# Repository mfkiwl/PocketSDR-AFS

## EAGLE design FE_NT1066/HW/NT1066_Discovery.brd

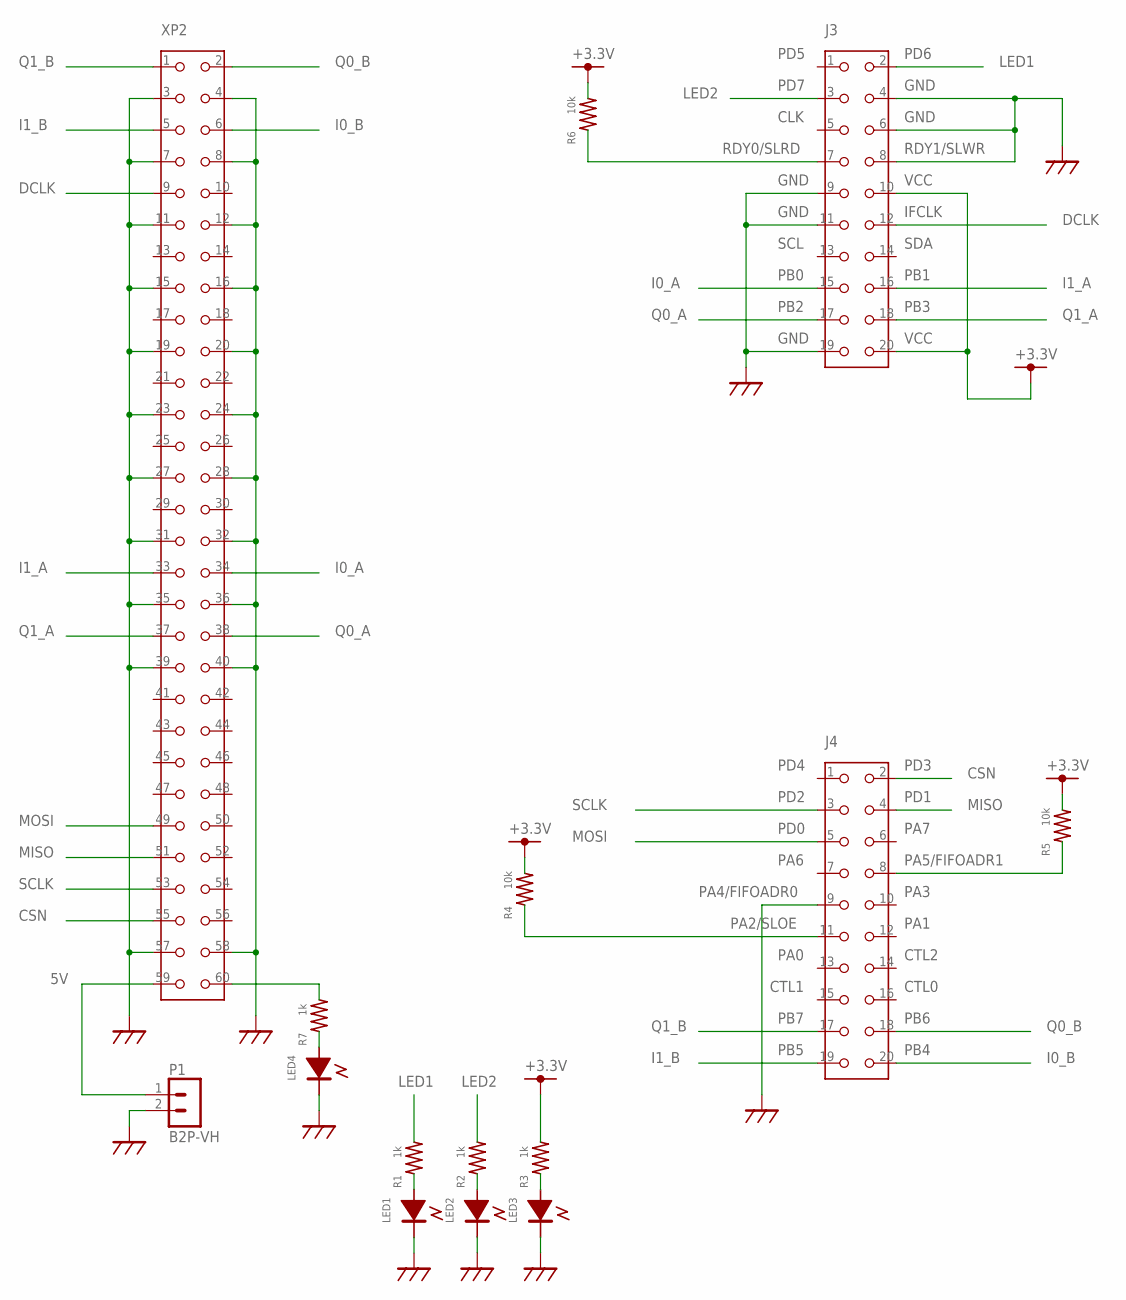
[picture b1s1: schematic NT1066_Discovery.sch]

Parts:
J3, J4: PINH-2.54MM-20P
LED1, LED2, LED3, LED4: LED1608; LED_1608
P1: B2P-VH
R1, R2, R3, R7: 1k; C1608
R4, R5, R6: 10k; C1608
XP2: PINH-2.54MM-60P

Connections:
5V: P1.1, XP2.59
+3.3V: J3.10, J3.20, R3.2, R4.2, R5.2, R6.2
CSN: J4.2, XP2.55
DCLK: J3.12, XP2.9
FIFOADR1: J4.8, R5.1
GND: J3.4, J3.6, J3.8, J3.9, J3.11, J3.19, J4.9, LED1.2, LED2.2, LED3.2, LED4.2, P1.2, XP2.3, XP2.4, XP2.7, XP2.8, XP2.11, XP2.12, XP2.15, XP2.16, XP2.19, XP2.20, XP2.23, XP2.24, XP2.27, XP2.28, XP2.31, XP2.32, XP2.35, XP2.36, XP2.39, XP2.40, XP2.57, XP2.58
I0_A: J3.15, XP2.34
I0_B: J4.20, XP2.6
I1_A: J3.16, XP2.33
I1_B: J4.19, XP2.5
LED1: J3.2, R1.2
LED2: J3.3, R2.2
MISO: J4.4, XP2.51
MOSI: J4.5, XP2.49
unnamed: R7.2, XP2.60
unnamed: LED4.1 (+), R7.1
unnamed: LED3.1 (+), R3.1
unnamed: LED2.1 (+), R2.1
unnamed: LED1.1 (+), R1.1
Q0_A: J3.17, XP2.38
Q0_B: J4.18, XP2.2
Q1_A: J3.18, XP2.37
Q1_B: J4.17, XP2.1
SCLK: J4.3, XP2.53
SLOE: J4.11, R4.1
SLRD: J3.7, R6.1

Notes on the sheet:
RDY1/SLWR
PD6
GND
VCC
IFCLK
SDA
PB1
PB3
PD5
PD7
CLK
RDY0/SLRD
SCL
PB0
PB2
PD4
PD2
PD0
PA6
PA4/FIFOADR0
PA2/SLOE
PA0
CTL1
PB7
PB5
PB4
PB6
CTL0
CTL2
PA1
PA3
PA5/FIFOADR1
PA7
PD1
PD3

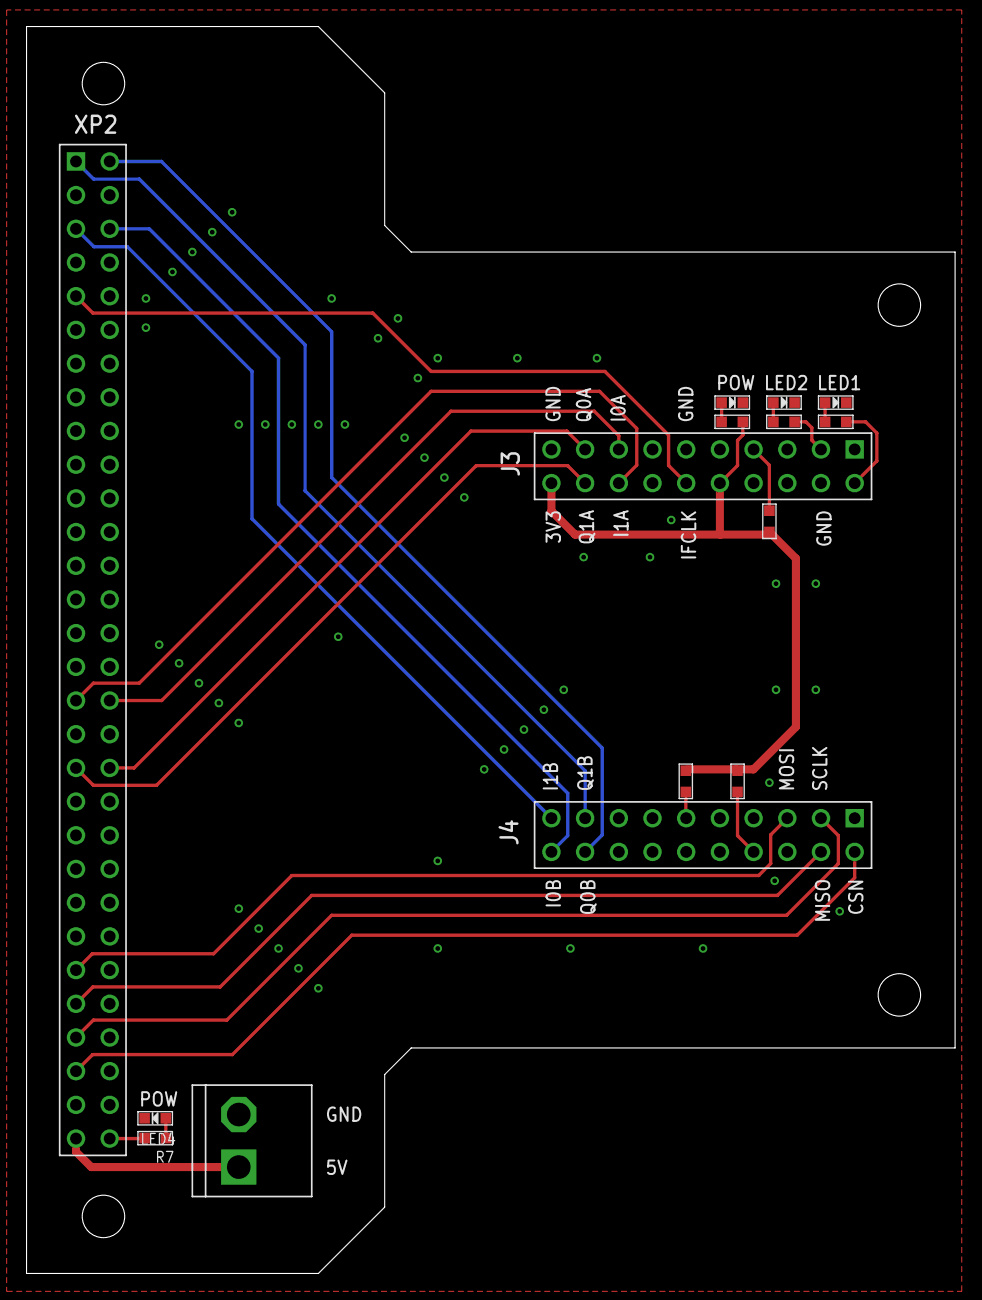
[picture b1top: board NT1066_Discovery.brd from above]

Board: 2 copper layers, 70.0 x 94.0 mm, 15 parts (0 on the bottom side), 26 nets.

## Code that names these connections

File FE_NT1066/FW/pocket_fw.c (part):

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#ifndef F_TCXO
#define F_TCXO       24000      // TCXO frequency (kHz)
#endif
#define CSN1         0          // EZ-USB FX2 PD0  -> MAX2771 CH1 CSN
#define CSN2         1          // EZ-USB FX2 PD1  -> MAX2771 CH2 CSN
#define SCLK         2          // EZ-USB FX2 PD2  -> MAX2771 SCLK
#define SDATA        3          // EZ-USB FX2 PD3 <-> MAX2771 SDATA
#define STAT1        4          // EZ-USB FX2 PD4 <-  MAX2771 CH1 LD
#define STAT2        5          // EZ-USB FX2 PD5 <-  MAX2771 CH2 LD
#define LED1         6          // EZ-USB FX2 PD6  -> LED1
#define LED2         7          // EZ-USB FX2 PD7  -> LED2
#define SCLK_CYC     5          // SPI SCLK delay

#define MOSI 0 // PD0 -> NT1066 MOSI
#define MISO 1 // PD1 <- NT1066 MISO
#define CSN  3 // PD3 -> NT1066 CSN

#define VR_STAT      0x40       // USB vendor request: Get device info and status
#define VR_REG_READ  0x41       // USB vendor request: Read MAX2771 register
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
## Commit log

2025-12-03 Fix segmentation fault in sdr_str_open
    Fixed segmentation fault by adding null check for 'p' before sscanf.
2025-12-04 Add NT1066 support
2026-04-07 SoapySDR support
2026-04-07 Add link to libSoapySDR
2026-04-08 Add SoapySDR support
2026-04-12 Add .gitignore
2026-04-12 Support SoapySDR
2026-04-13 Add SoapySDR options
2026-04-14 SoapySDR demo
2026-04-18 Update reader_thread
2026-04-19 Add max Doppler option
